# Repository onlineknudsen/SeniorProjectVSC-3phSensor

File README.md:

View this project on [CADLAB.io](https://cadlab.io/project/28017).

# Senior Project - Voltage Sourced Converter - 3 phase Power Sensor
### Lin Knudsen, Thomas Mack, Nikhil Patel
Chip: Atmel M90E32AS Enhanced Poly-Phase High-Performance Wide-Span
Energy Metering IC

[Datasheet](https://ww1.microchip.com/downloads/aemDocuments/documents/OTH/ProductDocuments/DataSheets/Atmel-46003-SE-M90E32AS-Datasheet.pdf)

[Application Notes](https://ww1.microchip.com/downloads/aemDocuments/documents/OTH/ApplicationNotes/ApplicationNotes/Atmel-46103-SE-M90E32AS-ApplicationNote.pdf)

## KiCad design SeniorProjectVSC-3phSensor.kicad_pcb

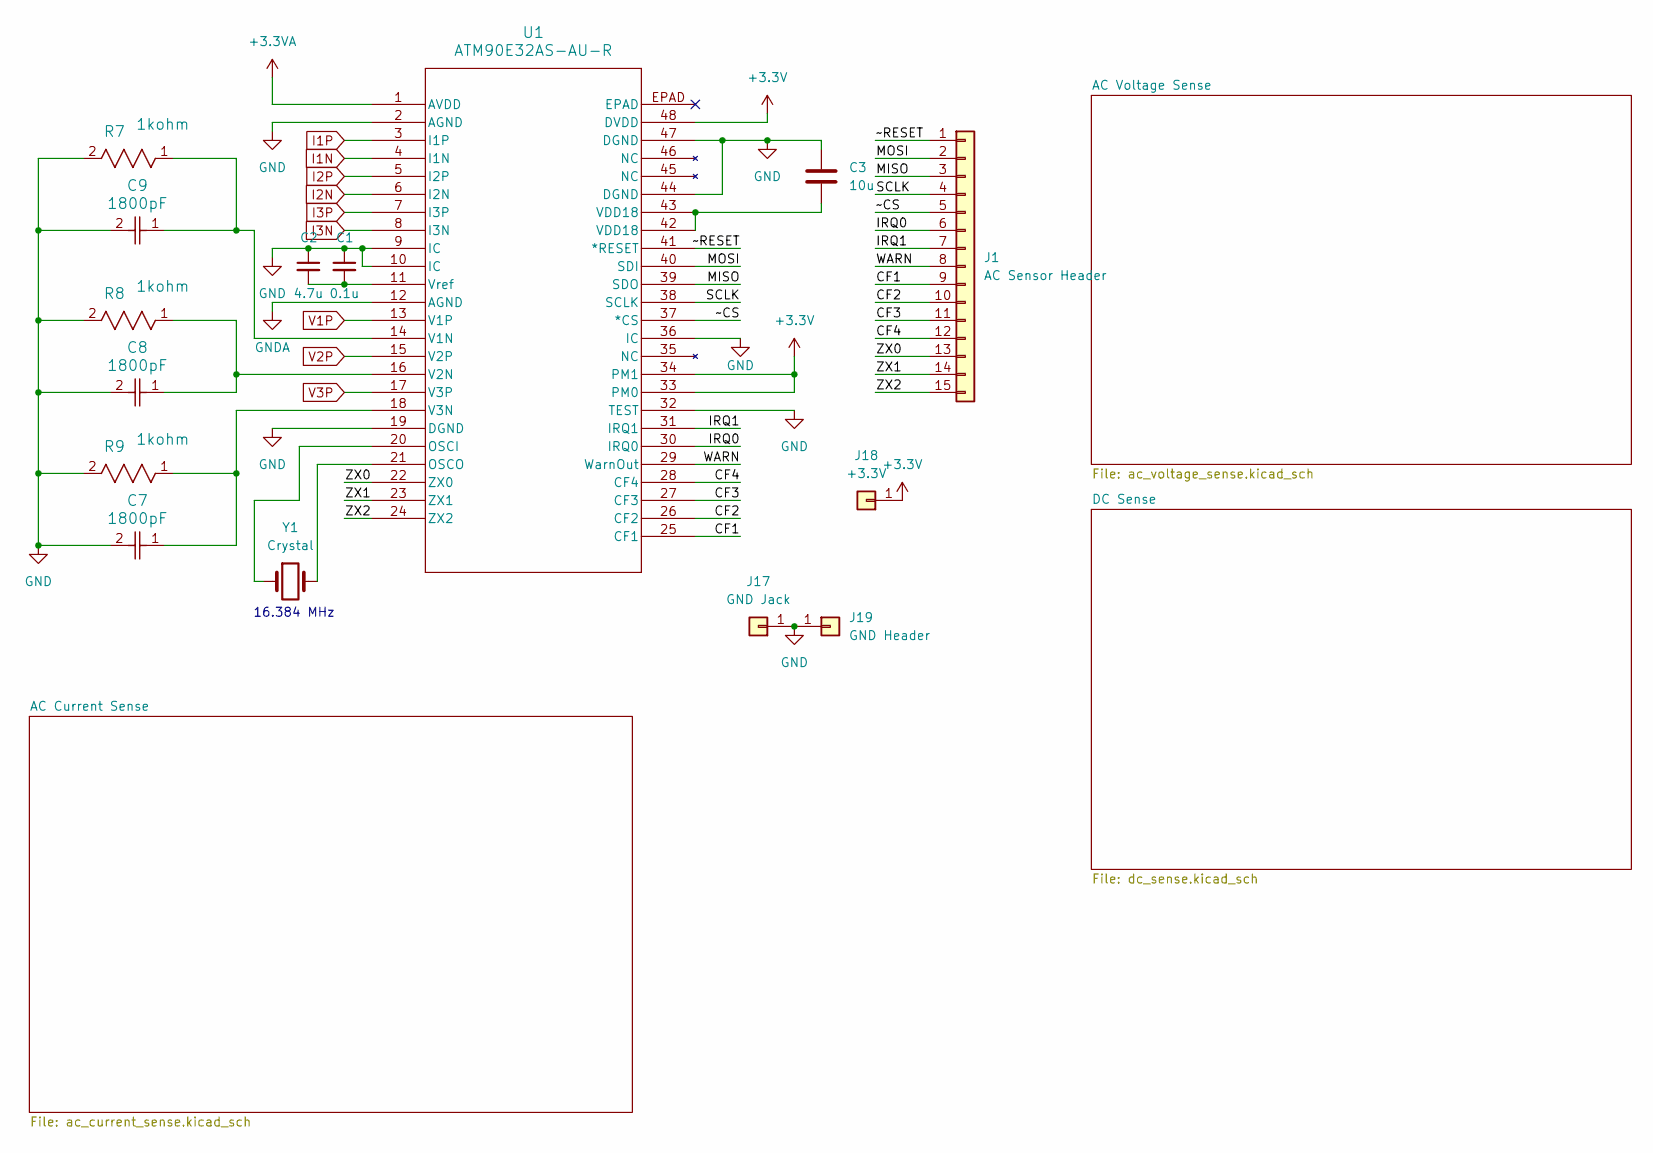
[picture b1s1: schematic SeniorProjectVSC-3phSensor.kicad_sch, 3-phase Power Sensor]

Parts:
C1: 0.1u; C_0805_2012Metric_Pad1.18x1.45mm_HandSolder
C2: 4.7u; C_0805_2012Metric_Pad1.18x1.45mm_HandSolder
C3: 10u; C_0805_2012Metric_Pad1.18x1.45mm_HandSolder
C7, C8, C9: 1800pF; C_0805_2012Metric_Pad1.18x1.45mm_HandSolder
J1: AC Sensor Header; PinHeader_1x15_P2.54mm_Vertical
J17: GND Jack; Banana_Jack_1Pin
J18: +3.3V; PinHeader_1x01_P2.54mm_Vertical
J19: GND Header; PinHeader_1x01_P2.54mm_Vertical
R7, R8, R9: 1kohm; R_0805_2012Metric_Pad1.20x1.40mm_HandSolder
U1: ATM90E32AS-AU-R; TQFP48_7x7MC_MCH-M
Y1: Crystal; XTAL_ABLS-16.384MHZ-B4-T

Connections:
+3.3V: J18.1, U1.33 (PM0), U1.34 (PM1), U1.48 (DVDD); also elsewhere on the board
+3.3VA: U1.1 (AVDD)
/CF1: J1.9, U1.25 (CF1)
/CF2: J1.10, U1.26 (CF2)
/CF3: J1.11, U1.27 (CF3)
/CF4: J1.12, U1.28 (CF4)
/IRQ0: J1.6, U1.30 (IRQ0)
/IRQ1: J1.7, U1.31 (IRQ1)
/MISO: J1.3, U1.39 (SDO)
/MOSI: J1.2, U1.40 (SDI)
/SCLK: J1.4, U1.38 (SCLK)
/WARN: J1.8, U1.29 (WarnOut)
/ZX0: J1.13, U1.22 (ZX0)
/ZX1: J1.14, U1.23 (ZX1)
/ZX2: J1.15, U1.24 (ZX2)
/~CS: J1.5, U1.37 (*CS)
/~RESET: J1.1, U1.41 (*RESET)
GND: C1.1, C2.1, C3.1, C7.2, C8.2, C9.2, J17.1, J19.1, R7.2, R8.2, R9.2, U1.2 (AGND), U1.9 (IC), U1.10 (IC), U1.19 (DGND), U1.32 (TEST), U1.36 (IC), U1.44 (DGND), U1.47 (DGND); also elsewhere on the board
GNDA: U1.12 (AGND)
I1N: U1.4 (I1N); also elsewhere on the board
I1P: U1.3 (I1P); also elsewhere on the board
I2N: U1.6 (I2N); also elsewhere on the board
I2P: U1.5 (I2P); also elsewhere on the board
I3N: U1.8 (I3N); also elsewhere on the board
I3P: U1.7 (I3P); also elsewhere on the board
unnamed: C3.2, U1.42 (VDD18), U1.43 (VDD18)
unnamed: U1.20 (OSCI), Y1.1
unnamed: U1.21 (OSCO), Y1.2
unnamed: C9.1, R7.1, U1.14 (V1N)
unnamed: C8.1, R8.1, U1.16 (V2N)
unnamed: C7.1, R9.1, U1.18 (V3N)
unnamed: C1.2, C2.2, U1.11 (Vref)
V1P: U1.13 (V1P); also elsewhere on the board
V2P: U1.15 (V2P); also elsewhere on the board
V3P: U1.17 (V3P); also elsewhere on the board

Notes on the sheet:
16.384 MHz

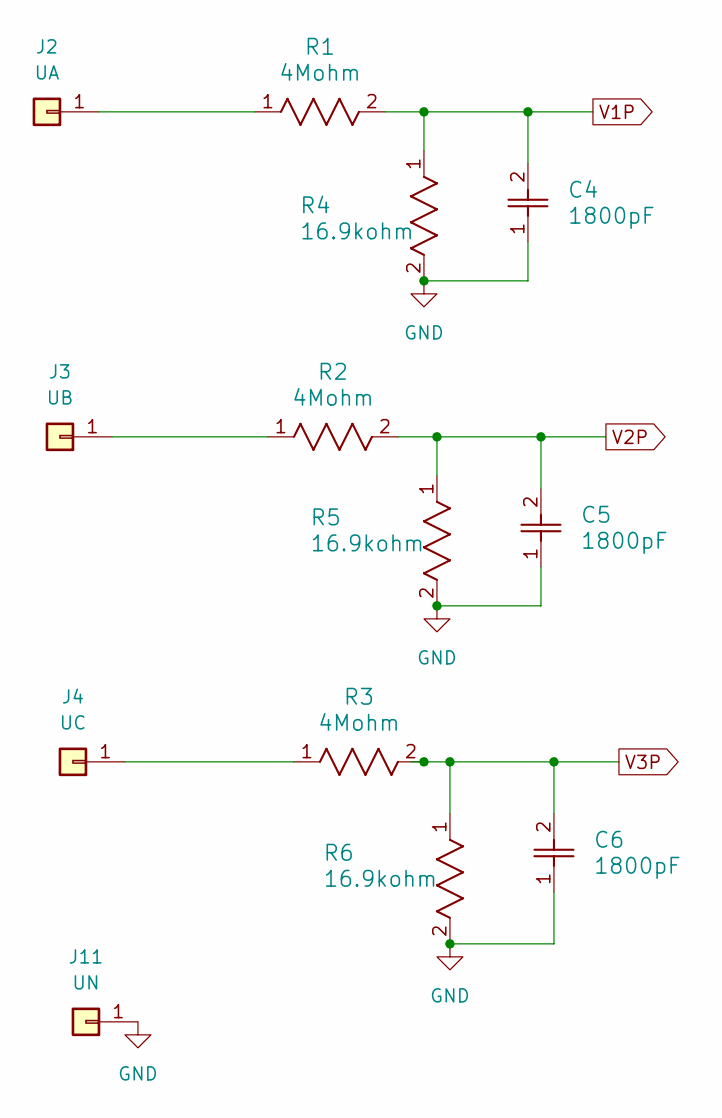
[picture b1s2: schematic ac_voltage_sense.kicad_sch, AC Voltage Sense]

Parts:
C4, C5, C6: 1800pF; C_0805_2012Metric_Pad1.18x1.45mm_HandSolder
J2: UA; Banana_Jack_1Pin
J3: UB; Banana_Jack_1Pin
J4: UC; Banana_Jack_1Pin
J11: UN; Banana_Jack_1Pin
R1, R2, R3: 4Mohm; R_0805_2012Metric_Pad1.20x1.40mm_HandSolder
R4, R5, R6: 16.9kohm; R_0805_2012Metric_Pad1.20x1.40mm_HandSolder

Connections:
GND: C4.1, C5.1, C6.1, J11.1, R4.2, R5.2, R6.2; also elsewhere on the board
unnamed: J2.1, R1.1
unnamed: J3.1, R2.1
unnamed: J4.1, R3.1
V1P: C4.2, R1.2, R4.1; also elsewhere on the board
V2P: C5.2, R2.2, R5.1; also elsewhere on the board
V3P: C6.2, R3.2, R6.1; also elsewhere on the board

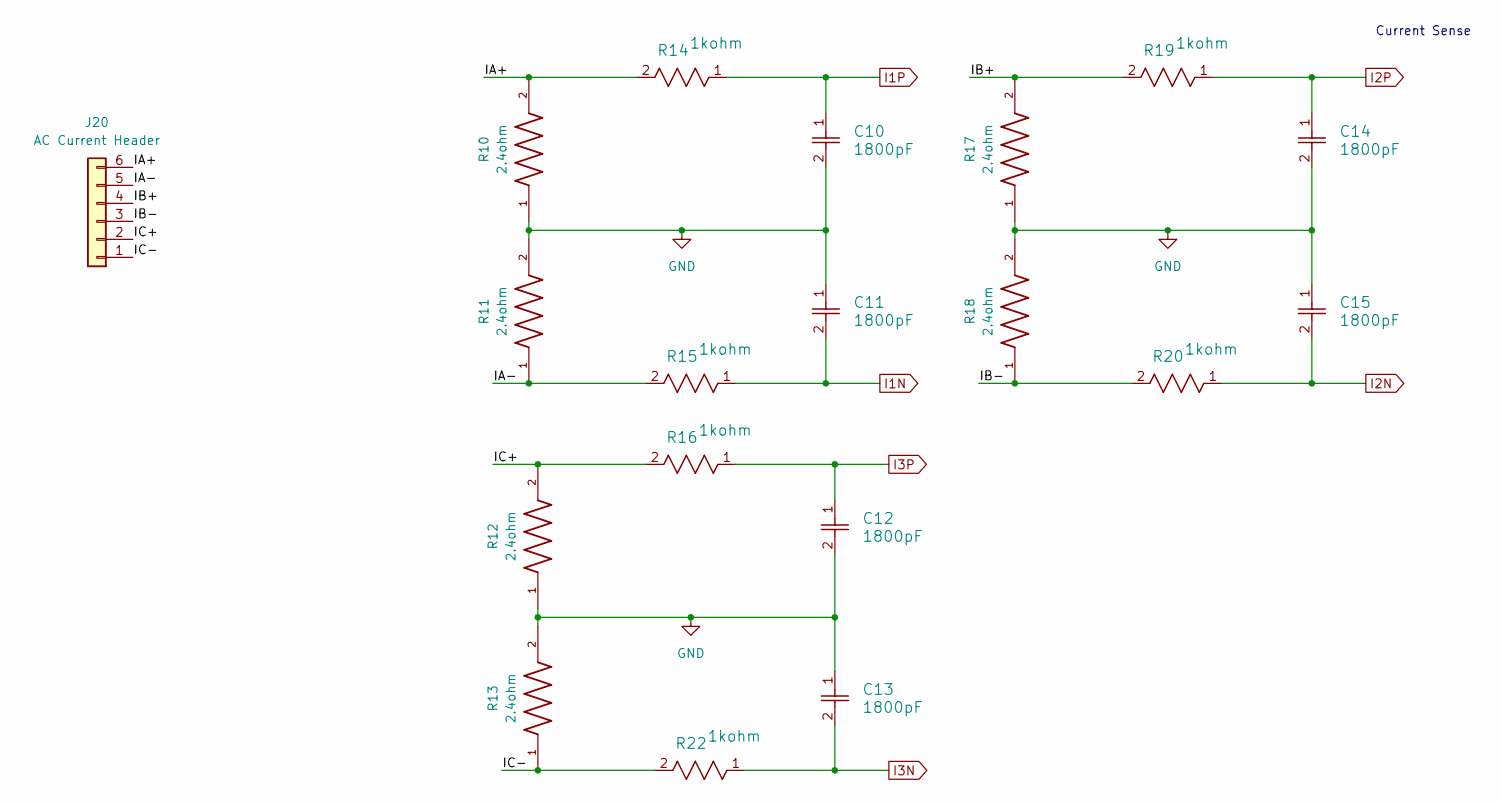
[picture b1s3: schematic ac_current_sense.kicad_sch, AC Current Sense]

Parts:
C10, C11, C12, C13, C14, C15: 1800pF; C_0805_2012Metric_Pad1.18x1.45mm_HandSolder
J20: AC Current Header; PinHeader_1x06_P2.54mm_Vertical
R10, R11, R12, R13, R17, R18: 2.4ohm; R_0805_2012Metric_Pad1.20x1.40mm_HandSolder
R14, R15, R16, R19, R20, R22: 1kohm; R_0805_2012Metric_Pad1.20x1.40mm_HandSolder

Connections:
/AC Current Sense/IA+: J20.6, R10.2, R14.2
/AC Current Sense/IA-: J20.5, R11.1, R15.2
/AC Current Sense/IB+: J20.4, R17.2, R19.2
/AC Current Sense/IB-: J20.3, R18.1, R20.2
/AC Current Sense/IC+: J20.2, R12.2, R16.2
/AC Current Sense/IC-: J20.1, R13.1, R22.2
GND: C10.2, C11.1, C12.2, C13.1, C14.2, C15.1, R10.1, R11.2, R12.1, R13.2, R17.1, R18.2; also elsewhere on the board
I1N: C11.2, R15.1; also elsewhere on the board
I1P: C10.1, R14.1; also elsewhere on the board
I2N: C15.2, R20.1; also elsewhere on the board
I2P: C14.1, R19.1; also elsewhere on the board
I3N: C13.2, R22.1; also elsewhere on the board
I3P: C12.1, R16.1; also elsewhere on the board

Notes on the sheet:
Current Sense

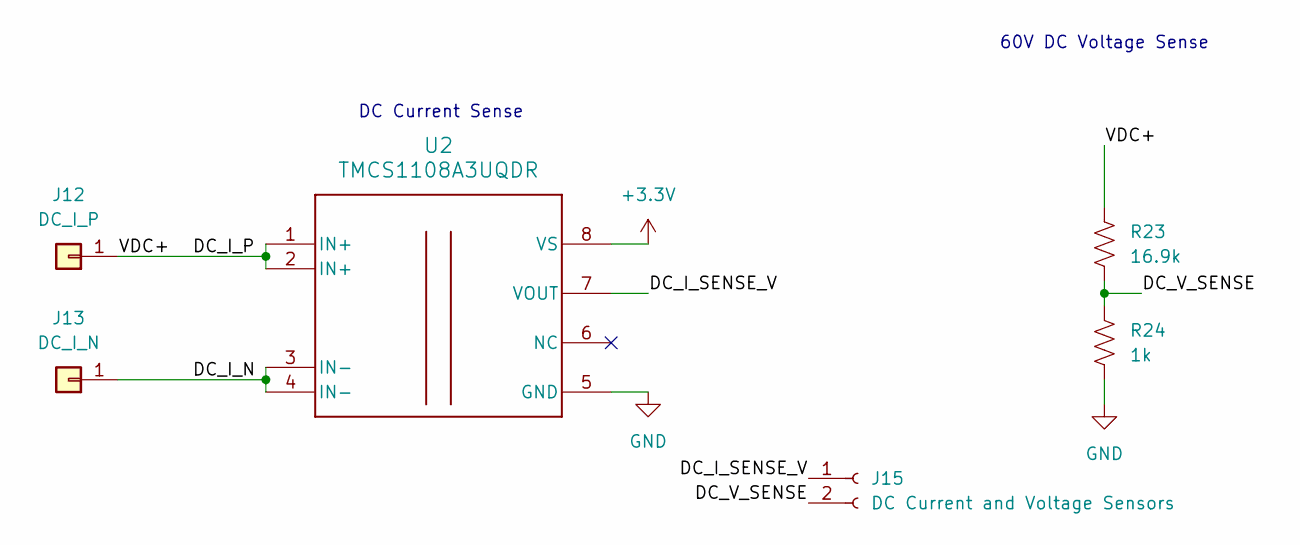
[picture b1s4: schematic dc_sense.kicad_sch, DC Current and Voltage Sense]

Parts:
J12: DC_I_P; Banana_Jack_1Pin
J13: DC_I_N; Banana_Jack_1Pin
J15: DC Current and Voltage Sensors; PinHeader_1x02_P2.54mm_Vertical
R23: 16.9k; R_0805_2012Metric_Pad1.20x1.40mm_HandSolder
R24: 1k; R_0805_2012Metric_Pad1.20x1.40mm_HandSolder
U2: TMCS1108A3UQDR; D0008A-IPC_A

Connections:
+3.3V: U2.8 (VS); also elsewhere on the board
/DC Sense/DC_I_N: J13.1, U2.3 (IN-), U2.4 (IN-)
/DC Sense/DC_I_P: J12.1, R23.1, U2.1 (IN+), U2.2 (IN+)
/DC Sense/DC_I_SENSE_V: J15.1, U2.7 (VOUT)
/DC Sense/DC_V_SENSE: J15.2, R23.2, R24.1
GND: R24.2, U2.5 (GND); also elsewhere on the board

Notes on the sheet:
60V DC Voltage Sense
DC Current Sense

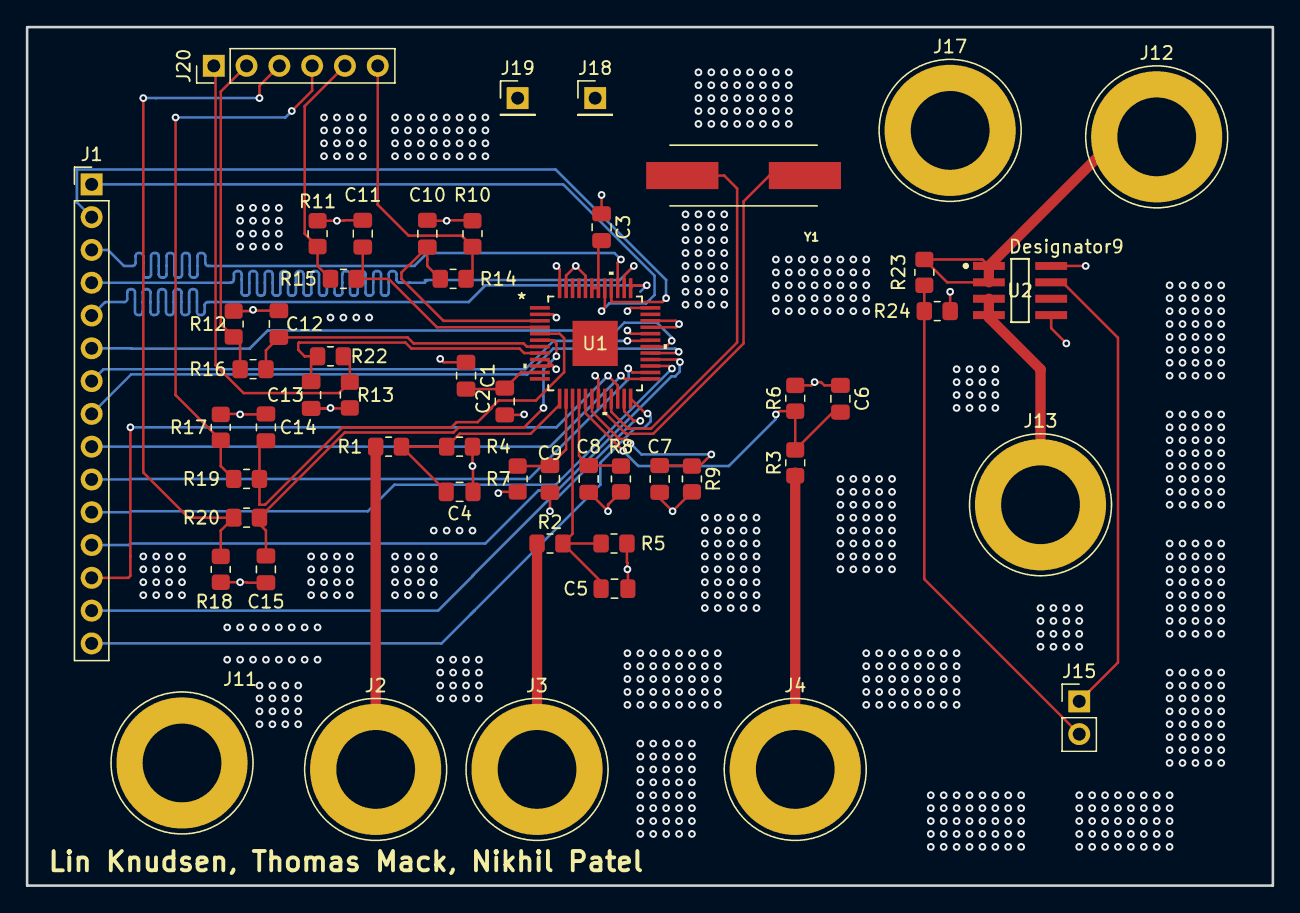
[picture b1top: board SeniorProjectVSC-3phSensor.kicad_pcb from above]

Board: 4 copper layers, 96.5 x 66.5 mm, 53 parts (0 on the bottom side), 46 nets.

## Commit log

2024-04-07 Backlink to CADLAB.io has been added.
2024-04-07 Update CADLAB.io message
2024-04-07 Add ATM90E32AS KiCad symbol
2024-04-08 Add M90E32AS IC and breakouts
2024-04-11 voltage and current circuit added
2024-04-14 Add voltage and current sensors
2024-04-15 Added OSC footprint and cleaned up names.
2024-04-17 Modularize schematic and add DC voltage and current sense
2024-04-19 PCB V1
